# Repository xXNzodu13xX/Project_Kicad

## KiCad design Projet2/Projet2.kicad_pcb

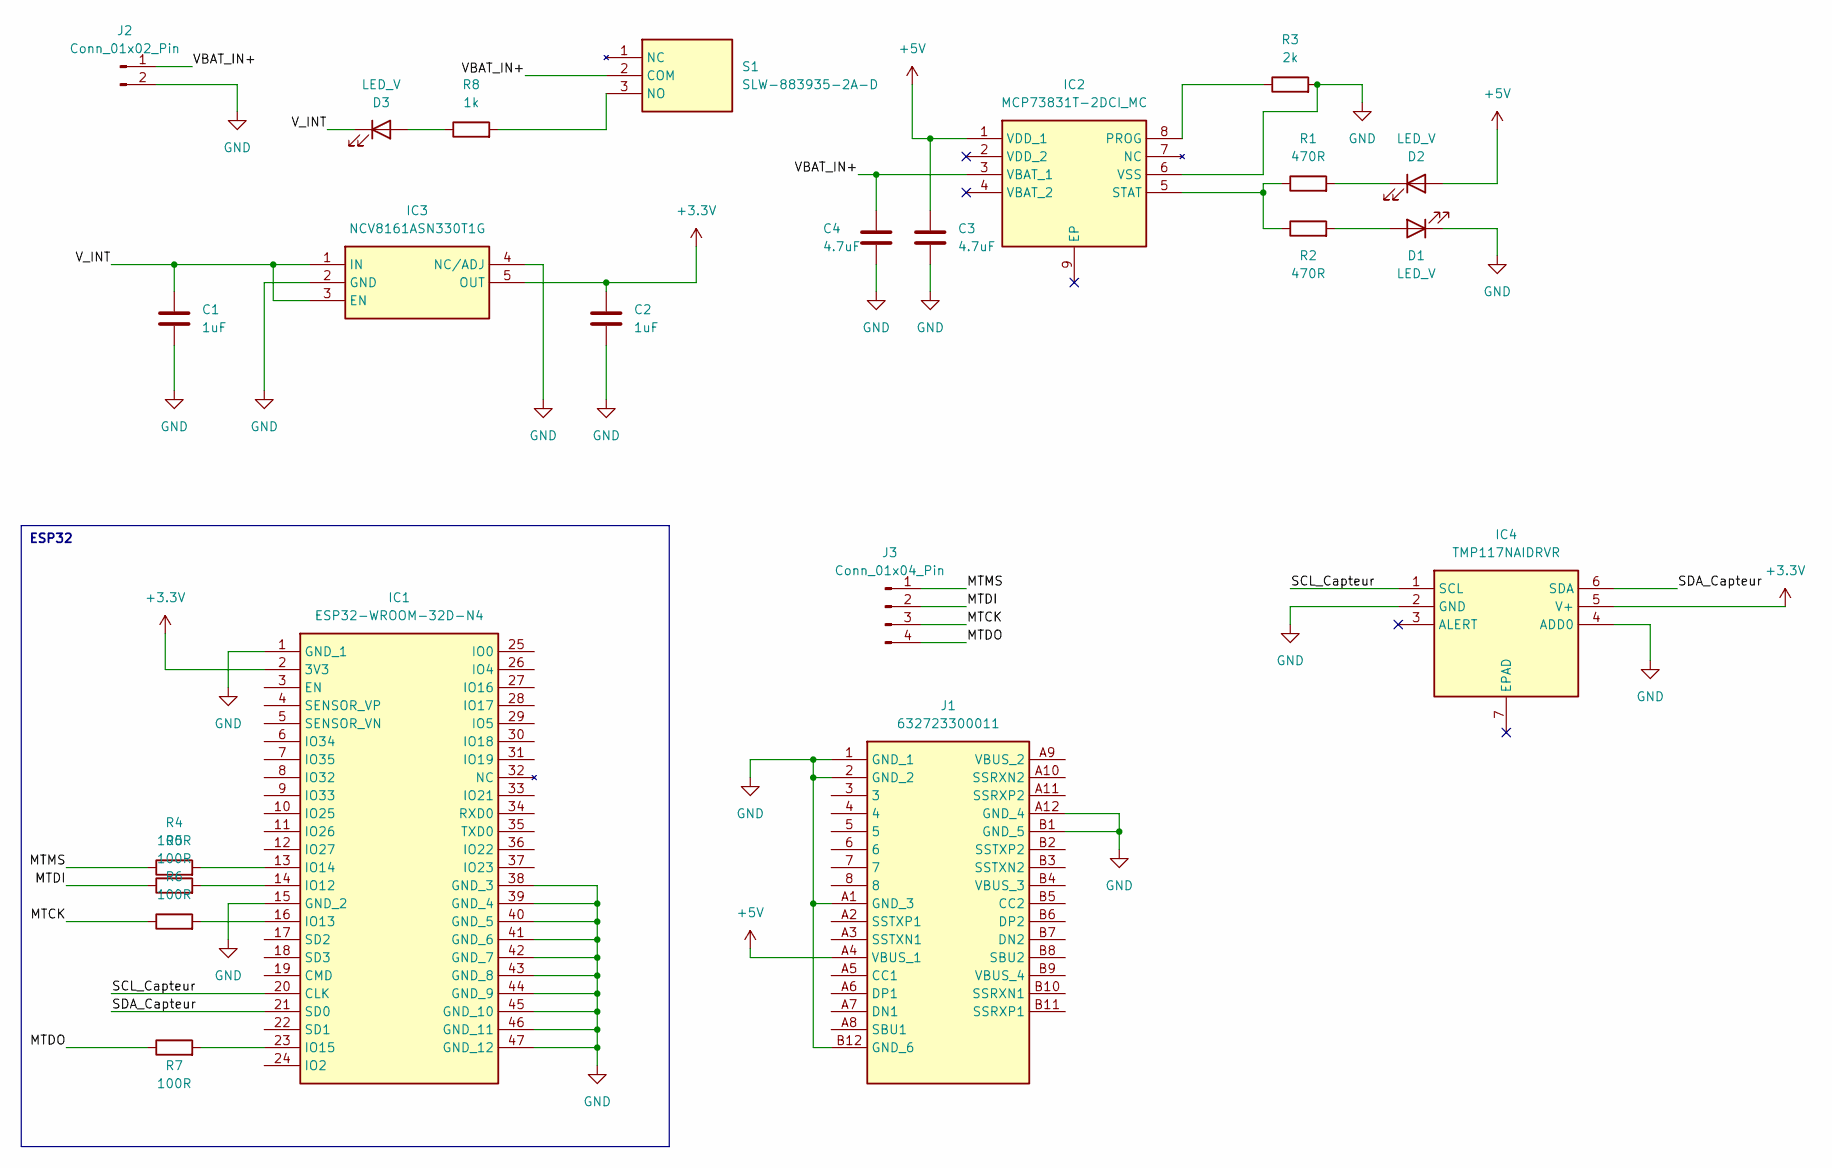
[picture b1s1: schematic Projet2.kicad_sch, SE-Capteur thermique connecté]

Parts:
C1, C2: 1uF; C_0402_1005Metric
C3, C4: 4.7uF; C_0402_1005Metric
D1, D2, D3: LED_V; LED_0201_0603Metric
IC1: ESP32-WROOM-32D-N4; ESP32WROOM32DN4; Mouser Part Number 356-ESP32WROOM-32D
IC2: MCP73831T-2DCI_MC; SON50P300X200X100-9N-D; Mouser Part Number 579-MCP73831T-2DCIMC
IC3: NCV8161ASN330T1G; SOT95P275X110-5N; Mouser Part Number 863-NCV8161ASN330T1G
IC4: TMP117NAIDRVR; SON65P200X200X80-7N; Mouser Part Number 595-TMP117NAIDRVR
J1: 632723300011; Mouser Part Number 710-632723300011
J2: Conn_01x02_Pin; JWT_A3963_1x02_P3.96mm_Vertical
J3: Conn_01x04_Pin; JST_EH_S4B-EH_1x04_P2.50mm_Horizontal
R1, R2: 470R; R_0402_1005Metric
R3: 2k; R_0402_1005Metric
R4, R5, R6, R7: 100R; R_0402_1005Metric
R8: 1k; R_0402_1005Metric
S1: SLW-883935-2A-D; SLW8839352AD; Mouser Part Number 179-SLW-883935-2A-D

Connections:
+3.3V: C2.1, IC1.2 (3V3), IC3.5 (OUT), IC4.5 (V+)
+5V: C3.2, D2.2 (A), IC2.1 (VDD_1), J1.A4 (VBUS_1)
/MTCK: J3.3, R6.1
/MTDI: J3.2, R5.1
/MTDO: J3.4, R7.1
/MTMS: J3.1, R4.1
/SCL_Capteur: IC1.20 (CLK), IC4.1 (SCL)
/SDA_Capteur: IC1.21 (SD0), IC4.6 (SDA)
/VBAT_IN+: C4.2, IC2.3 (VBAT_1), J2.1, S1.2 (COM)
/V_INT: C1.1, D3.1 (K), IC3.1 (IN), IC3.3 (EN)
GND: C1.2, C2.2, C3.1, C4.1, D1.1 (K), IC1.1 (GND_1), IC1.15 (GND_2), IC1.38 (GND_3), IC1.39 (GND_4), IC1.40 (GND_5), IC1.41 (GND_6), IC1.42 (GND_7), IC1.43 (GND_8), IC1.44 (GND_9), IC1.45 (GND_10), IC1.46 (GND_11), IC1.47 (GND_12), IC2.6 (VSS), IC3.2 (GND), IC3.4 (NC/ADJ), IC4.2 (GND), IC4.4 (ADD0), J1.1 (GND_1), J1.2 (GND_2), J1.A1 (GND_3), J1.A12 (GND_4), J1.B1 (GND_5), J1.B12 (GND_6), J2.2, R3.2
unnamed: D1.2 (A), R2.2
unnamed: D2.1 (K), R1.2
unnamed: D3.2 (A), R8.1
unnamed: IC1.14 (IO12), R5.2
unnamed: IC1.16 (IO13), R6.2
unnamed: IC1.13 (IO14), R4.2
unnamed: IC1.23 (IO15), R7.2
unnamed: IC2.8 (PROG), R3.1
unnamed: IC2.5 (STAT), R1.1, R2.1
unnamed: R8.2, S1.3 (NO)

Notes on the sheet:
ESP32

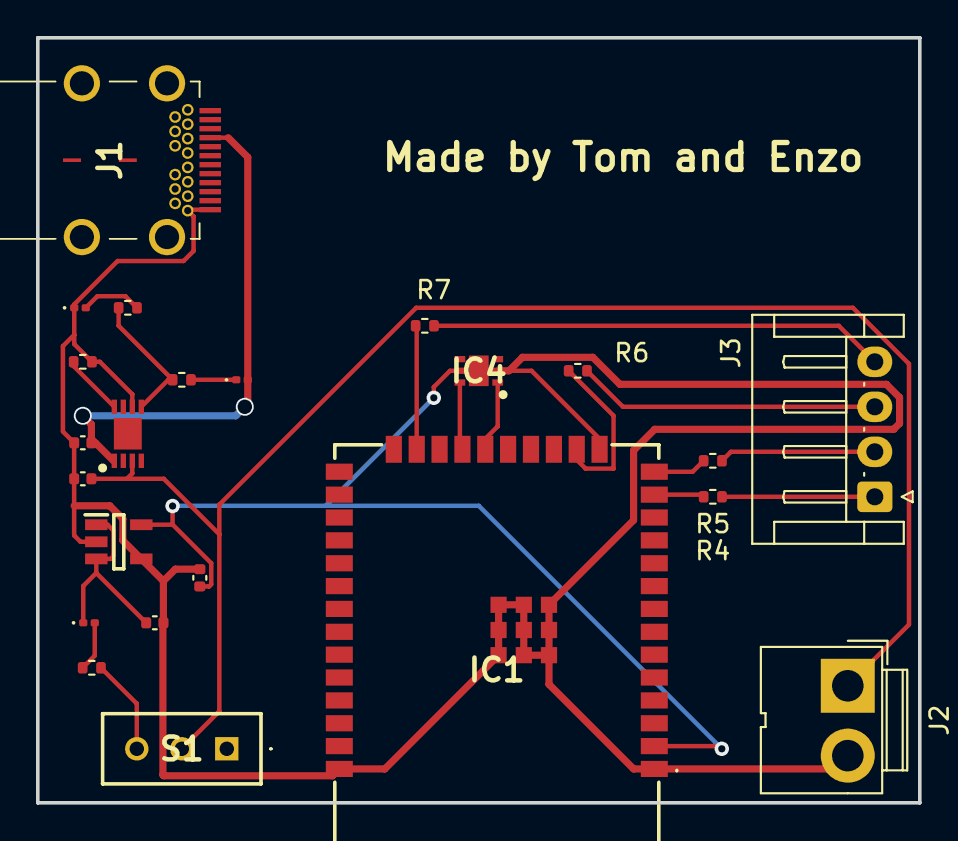
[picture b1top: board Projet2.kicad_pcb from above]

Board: 2 copper layers, 49.0 x 42.5 mm, 23 parts (0 on the bottom side), 21 nets.

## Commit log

2023-10-25 Project IOT by Enzo De Cock and Tom Faulque
    Version 1.0
2023-10-25 Rapport IOT
    Version 1.0
